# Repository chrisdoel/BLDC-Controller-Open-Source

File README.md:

# BLDC-Controller-Open-Source
An Open Source BLDC motor speed controller, created from scratch, which supports both sensored and sensorless motors. The full schematic, hardware, code and documentation has been provided.

# Please refer to [Documentation.pdf](/Documentation.pdf) for the complete documentation, theory behding the BLDC controller and construction instructions

# The Schematic

# An assembled BLDC controller

 # The PCB
 
|  |  |
|:---:|:---:|

# A large sensored motor setup being driven by two BLDC controllers
https://user-images.githubusercontent.com/70950249/136831820-4237cd56-f56c-432a-8c37-596cbc5fa2e3.mp4

# A sensorless motor being driven by the BLDC controller
https://user-images.githubusercontent.com/70950249/136831950-987a125a-ef0f-476e-b4f4-f5f6af1766f3.mp4

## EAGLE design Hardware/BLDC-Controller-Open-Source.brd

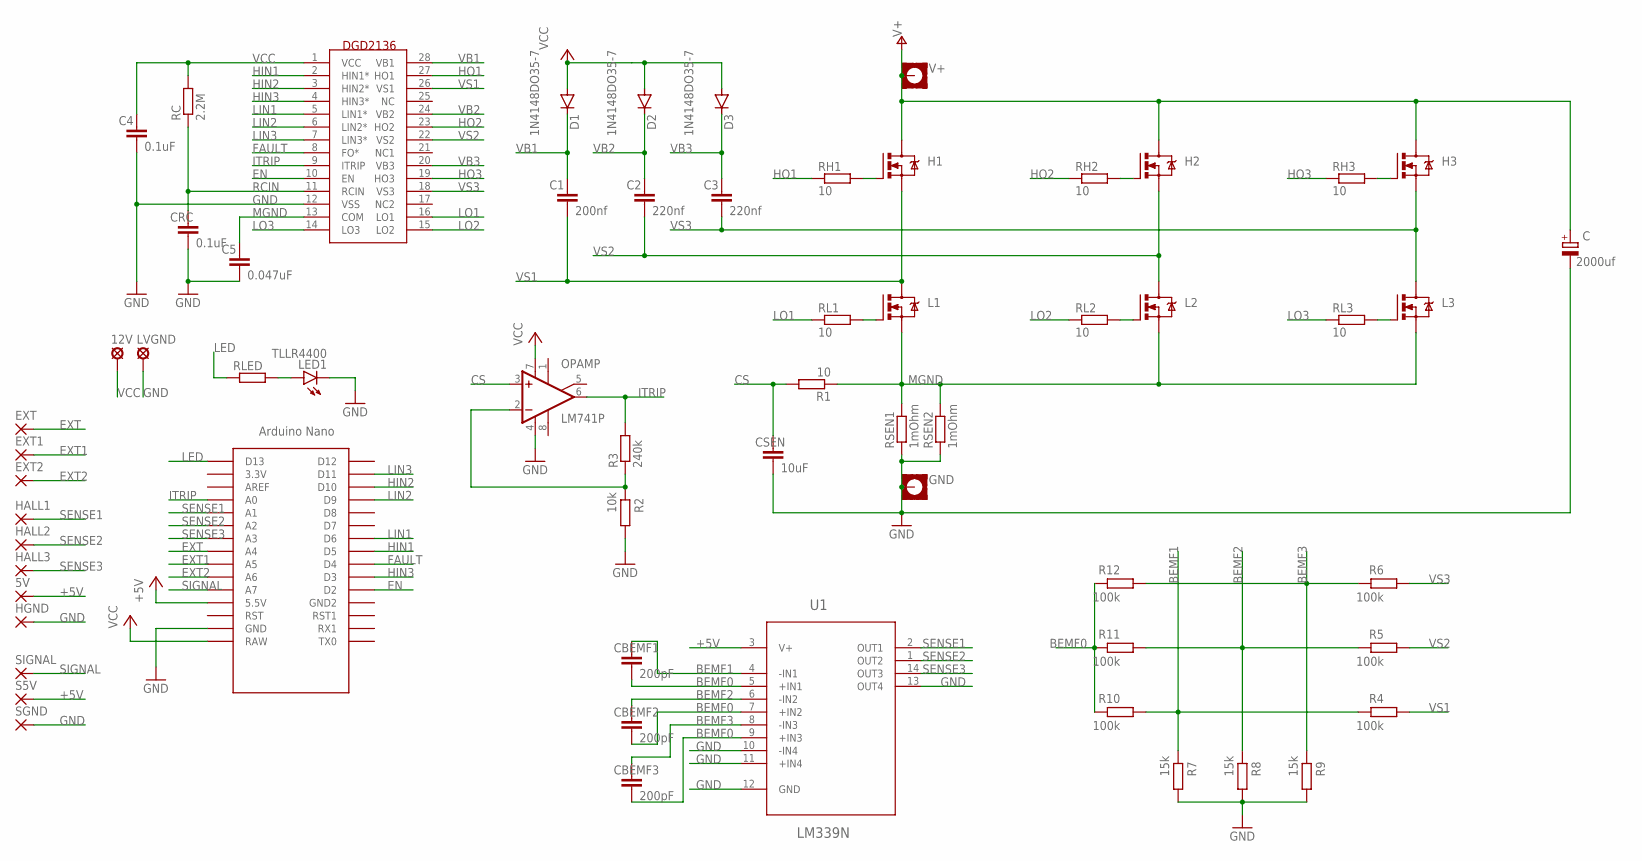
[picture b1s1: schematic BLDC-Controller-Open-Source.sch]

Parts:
5V: 1,6/0,9
12V: MCS10B
C: 2000uf; E7,5-16
C1: 200nf; C025-025X050
C2, C3: 220nf; C025-025X050
C4: 0.1uF; C025-025X050
C5: 0.047uF; C025-025X050
CBEMF1, CBEMF2, CBEMF3: 200pF; C025-025X050
CRC: 0.1uF; C025-025X050
CSEN: 10uF; C025-025X050
D1, D2, D3: 1N4148DO35-7; DO35-7
EXT, EXT1, EXT2: 1,6/0,9
GND: MOUNT-PAD-SQUARE3.6; 3,6-PAD-SQUARE
H1, H2, H3: IRF540; TO220BV
HALL1, HALL2, HALL3: 1,6/0,9
HGND: 1,6/0,9
L1, L2, L3: IRF540; TO220BV
LED1: TLLR4400; LED3MM
LVGND: MCS10B
OPAMP: LM741P; DIL08
R1: 10; 0204/7
R2: 10k; 0204/7
R3: 240k; 0204/7
R4, R5, R6, R10, R11, R12: 100k; 0204/7
R7, R8, R9: 15k; 0204/7
RC: 2.2M; 0204/7
RH1, RH2, RH3: 10; 0204/7
RL1, RL2, RL3: 10; 0204/7
RLED: R-EU_0204/7; 0204/7
RSEN1, RSEN2: 1mOhm; R2512
S5V: 1,6/0,9
SGND: 1,6/0,9
SIGNAL: 1,6/0,9
U1: LM339N; DIP254P762X508-14
U$1: NANO
U$2: DGD2136
V+: MOUNT-PAD-SQUARE3.6; 3,6-PAD-SQUARE

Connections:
+5V: 5V.1, S5V.1, U1.3 (V+), U$1.5V (5.5V)
BEMF0: CBEMF1.2, CBEMF2.2, CBEMF3.2, R10.2, R11.2, R12.2, U1.5 (+IN1), U1.7 (+IN2), U1.9 (+IN3)
BEMF1: CBEMF1.1, R4.2, R7.2, R10.1, U1.4 (-IN1)
BEMF2: CBEMF2.1, R5.2, R8.2, R11.1, U1.6 (-IN2)
BEMF3: CBEMF3.1, R6.2, R9.2, R12.1, U1.8 (-IN3)
CS: CSEN.1, OPAMP.3 (+IN), R1.2
EN: U$1.D2, U$2.10 (EN)
EXT: EXT.1, U$1.A4
EXT1: EXT1.1, U$1.A5
EXT2: EXT2.1, U$1.A6
FAULT: U$1.D4, U$2.8 (FO*)
GND: C.-, C4.2, C5.2, CRC.2, CSEN.2, GND.B3,6, HGND.1, LED1.K (C), LVGND.MP, OPAMP.4 (V-), R2.1, R7.1, R8.1, R9.1, RSEN1.1, RSEN2.1, SGND.1, U1.10 (-IN4), U1.11 (+IN4), U1.12 (GND), U1.13 (OUT4), U$1.GND, U$2.12 (VSS)
HIN1: U$1.D5, U$2.2 (HIN1*)
HIN2: U$1.D10, U$2.3 (HIN2*)
HIN3: U$1.D3, U$2.4 (HIN3*)
HO1: RH1.1, U$2.27 (HO1)
HO2: RH2.1, U$2.23 (HO2)
HO3: RH3.1, U$2.19 (HO3)
ITRIP: OPAMP.6 (OUT), R3.2, U$1.A0, U$2.9 (ITRIP)
LED: RLED.1, U$1.D13
LIN1: U$1.D6, U$2.5 (LIN1*)
LIN2: U$1.D9, U$2.6 (LIN2*)
LIN3: U$1.D11, U$2.7 (LIN3*)
LO1: RL1.1, U$2.16 (LO1)
LO2: RL2.1, U$2.15 (LO2)
LO3: RL3.1, U$2.14 (LO3)
MGND: C5.1, L1.S, L2.S, L3.S, R1.1, RSEN1.2, RSEN2.2, U$2.13 (COM)
unnamed: L3.G, RL3.2
unnamed: H3.G, RH3.2
unnamed: L1.G, RL1.2
unnamed: L2.G, RL2.2
unnamed: H2.G, RH2.2
unnamed: H1.G, RH1.2
unnamed: OPAMP.2 (-IN), R2.2, R3.1
unnamed: LED1.A, RLED.2
RCIN: CRC.1, RC.1, U$2.11 (RCIN)
SENSE1: HALL1.1, U1.2 (OUT1), U$1.A1
SENSE2: HALL2.1, U1.1 (OUT2), U$1.A2
SENSE3: HALL3.1, U1.14 (OUT3), U$1.A3
SIGNAL: SIGNAL.1, U$1.A7
V+: C.+, H1.D, H2.D, H3.D, V+.B3,6
VB1: C1.1, D1.C, U$2.28 (VB1)
VB2: C2.1, D2.C, U$2.24 (VB2)
VB3: C3.1, D3.C, U$2.20 (VB3)
VCC: 12V.MP, C4.1, D1.A, D2.A, D3.A, OPAMP.7 (V+), RC.2, U$1.RAW, U$2.1 (VCC)
VS1: C1.2, H1.S, L1.D, R4.1, U$2.26 (VS1)
VS2: C2.2, H2.S, L2.D, R5.1, U$2.22 (VS2)
VS3: C3.2, H3.S, L3.D, R6.1, U$2.18 (VS3)

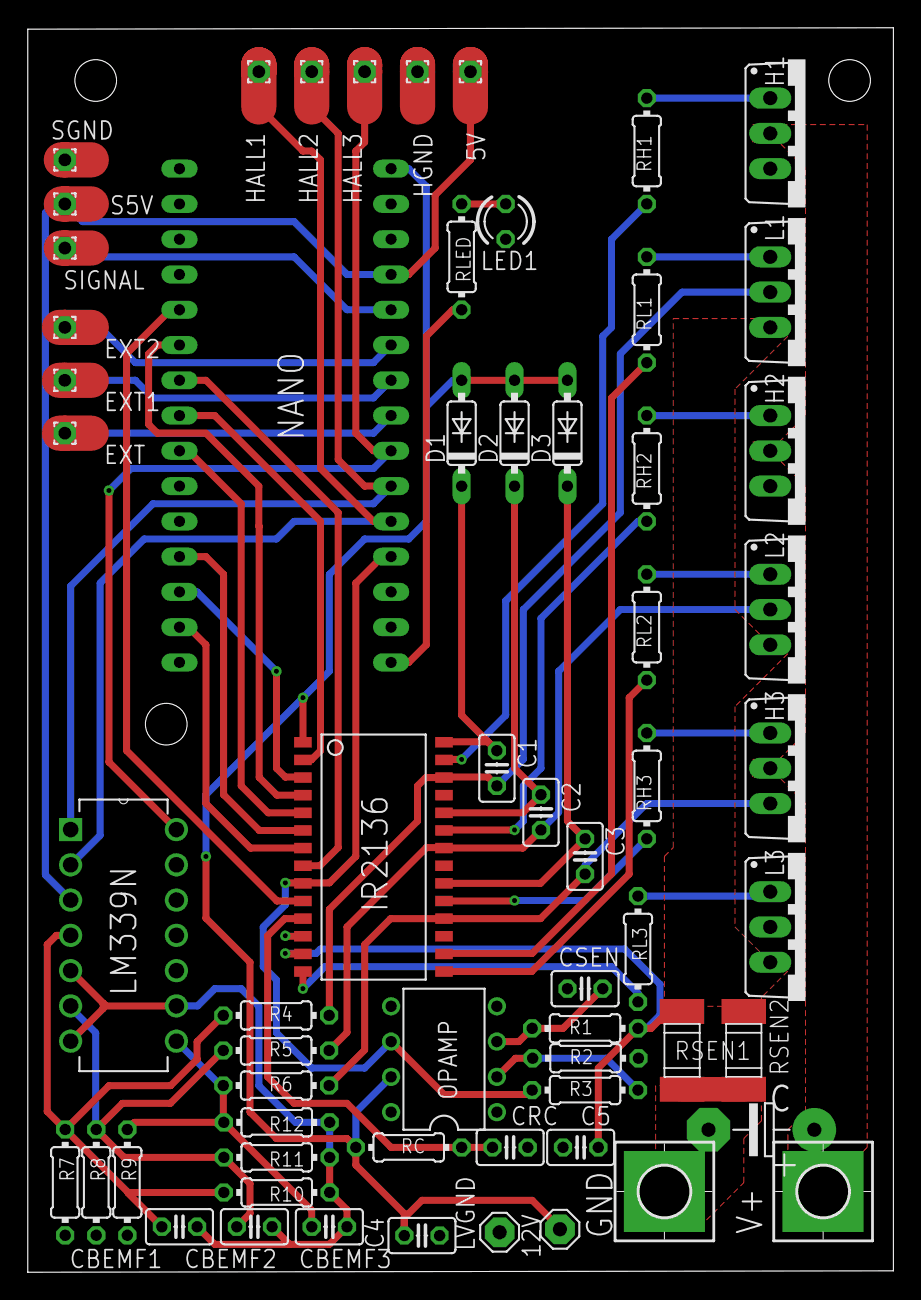
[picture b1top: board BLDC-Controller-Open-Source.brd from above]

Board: 2 copper layers, 62.3 x 89.6 mm, 62 parts (0 on the bottom side), 48 nets.

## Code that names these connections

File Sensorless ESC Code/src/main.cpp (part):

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
#define EN PORTD2

#define SENSE3 PORTC3
#define SENSE2 PORTC2
#define SENSE1 PORTC1

#define lowMax 0x00
#define lowMin 0xFF
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
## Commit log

2021-10-05 Added example images/videos, the first iteration of the documentation, code for sensored and sensorless operation, the schematic and board files
2021-10-05 Added hardware files
